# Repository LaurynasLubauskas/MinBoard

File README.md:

# MinBoard
Creator: Laurynas Lubauskas
<br>
Maintainer: Laurynas Lubauskas
<br>
MinBoard is a mini 3x3 keyboard that can *literally* fit in your pocket and is a way cheaper option than a streamdeck.
## About The Project
I made this project, because I am love fiddeling with tech and I hope it will be fun to build. This project was fun to make. It is my first "big" project. It had it's ups and downs, which I liked. In the future I might make another version of the MinBoard but that could happen in the distant future. This project has minimal codind required so if you are not familiar with coding don't worry. I think this would be a fun project for anyone who like diy or fiddeling with tech.
## Components
MinBoard contains 9 keys in total. My version of it uses the "Cherry MX Red" switches, but you can use your prefered switches. The whole keyboard is controlled by a "Seeed XIAO RP2040" microcontroller using qmk software. My version of this keyboard will use the transparent black keycaps, I think they are a great choice as they look minimalistic and have no stickers on so you have the freedom to change each button to your preference. As it is my first project I will use an easier type of diodes, the "1N4148 DO-35" because this will be my first time soldering anything.
>The PCB

---

>The Schematics

---

>3d Case

---

>3d Plate

## Contact Me
If you have any questions don't hesitate to contact me via Email
<br>
Email: laurynas.lubauskas@gmail.com

## BOM

| **Quantity** | **Item**                            | **Price**         | **Link**                                                                                                                                                                                                                                                                                                                                                                     |
| ------------ | ----------------------------------- | ----------------- | ---------------------------------------------------------------------------------------------------------------------------------------------------------------------------------------------------------------------------------------------------------------------------------------------------------------------------------------------------------------------------- |
| 9            | Cherry MX Red Switches              | 4.41€ / 5.08$     | [Link](https://fr.aliexpress.com/item/1005007891400560.htmlmp=1&pdp_npi=5@dis!EUR!EUR%204.41!EUR%204.41!!EUR%204.41!!!@211b655217621227696674886ed64a!12000042740647793!ct!LU!6001686758!!1!0&_gl=1*a0o1rq*_gcl_au*MzUxMzgzNTMyLjE3NjIwMzE5Mjc.*_ga*NjMyNjk0MjQ1LjE3NjIwMzE5Mjc.*_ga_VED1YSGNC7*czE3NjIxMjIxNTkkbzUkZzEkdDE3NjIxMjI3NjkkajI4JGwwJGgw&gatewayAdapt=glo2fra)   |
| 9            | 1N4148 DO-35 Diodes                 | 2.14€ / 2.47$     | [Link](https://fr.aliexpress.com/item/1005009623489970.html?mp=1&pdp_npi=5@dis!EUR!EUR%204.47!EUR%202.14!!EUR%202.14!!!@211b655217621227696674886ed64a!12000049679669844!ct!LU!6001686758!!1!0&_gl=1*1r24189*_gcl_au*MzUxMzgzNTMyLjE3NjIwMzE5Mjc.*_ga*NjMyNjk0MjQ1LjE3NjIwMzE5Mjc.*_ga_VED1YSGNC7*czE3NjIxMjIxNTkkbzUkZzEkdDE3NjIxMjMwMjkkajYwJGwwJGgw&gatewayAdapt=glo2fra) |
| 1            | Seeed Xiao RP2040                   | 6.99€ / 8.05$     | [Link](https://fr.aliexpress.com/item/1005003901735765.html?mp=1&pdp_npi=5@dis!EUR!EUR%2010.92!EUR%206.99!!EUR%206.99!!!@211b655217621227696674886ed64a!12000027424449312!ct!LU!6001686758!!1!0&_gl=1*o3cj8t*_gcl_au*MzUxMzgzNTMyLjE3NjIwMzE5Mjc.*_ga*NjMyNjk0MjQ1LjE3NjIwMzE5Mjc.*_ga_VED1YSGNC7*czE3NjIxMjIxNTkkbzUkZzEkdDE3NjIxMjMwNjYkajIzJGwwJGgw&gatewayAdapt=glo2fra) |
| 9            | Black-Transparent Keycaps           | 3.18€ / 3.66$     | [Link](https://fr.aliexpress.com/item/1005005514406952.html?mp=1&pdp_npi=5@dis!EUR!EUR%203.18!EUR%203.18!!EUR%203.18!!!@211b655217621227696674886ed64a!12000033372744478!ct!LU!6001686758!!1!0&_gl=1*bu5ilb*_gcl_au*MzUxMzgzNTMyLjE3NjIwMzE5Mjc.*_ga*NjMyNjk0MjQ1LjE3NjIwMzE5Mjc.*_ga_VED1YSGNC7*czE3NjIxMjIxNTkkbzUkZzEkdDE3NjIxMjMwNzIkajE3JGwwJGgw&gatewayAdapt=glo2fra)  |
| 1            | 3d Printed Case                     | N/A               | N/A                                                                                                                                                                                                                                                                                                                                                                          |
| 1            | 3d Printed Plate                    | N/A               | N/A                                                                                                                                                                                                                                                                                                                                                                          |
| 4            | M2 6mm Screws                       | 1.41€ / 1.62$     | [Link](https://fr.aliexpress.com/item/1005007264845313.html?mp=1&pdp_npi=5@dis!EUR!EUR%201.49!EUR%201.41!!EUR%201.41!!!@211b655217621227696674886ed64a!12000039998989024!ct!LU!6001686758!!1!0&_gl=1*1tnw096*_gcl_au*MzUxMzgzNTMyLjE3NjIwMzE5Mjc.*_ga*NjMyNjk0MjQ1LjE3NjIwMzE5Mjc.*_ga_VED1YSGNC7*czE3NjIxMjIxNTkkbzUkZzEkdDE3NjIxMjMxMDEkajYwJGwwJGgw&gatewayAdapt=glo2fra) |
| 4            | M2 8mm Standoffs                    | 1.87€ / 2.15$     | [Link](https://fr.aliexpress.com/item/1005007526941573.html?mp=1&pdp_npi=5@dis!EUR!EUR%202.01!EUR%201.87!!EUR%201.87!!!@211b655217621227696674886ed64a!12000041166342257!ct!LU!6001686758!!1!0&_gl=1*1ym2fc9*_gcl_au*MzUxMzgzNTMyLjE3NjIwMzE5Mjc.*_ga*NjMyNjk0MjQ1LjE3NjIwMzE5Mjc.*_ga_VED1YSGNC7*czE3NjIxMjIxNTkkbzUkZzEkdDE3NjIxMjMyNjMkajU5JGwwJGgw&gatewayAdapt=glo2fra) |
| 4            | Rubber Feet                         | 3.10€ / 3.57$     | [Link](https://fr.aliexpress.com/item/1005004068119765.html?mp=1&pdp_npi=5@dis!EUR!EUR%203.10!EUR%203.10!!EUR%203.10!!!@211b655217621227696674886ed64a!12000027931007348!ct!LU!6001686758!!1!0&_gl=1*av4qe7*_gcl_au*MzUxMzgzNTMyLjE3NjIwMzE5Mjc.*_ga*NjMyNjk0MjQ1LjE3NjIwMzE5Mjc.*_ga_VED1YSGNC7*czE3NjIxMjIxNTkkbzUkZzEkdDE3NjIxMjMyODUkajM3JGwwJGgw&gatewayAdapt=glo2fra)  |
| 1            | Pcb                                 | 6.85€ / 7.90$     | Photo in img folder                                                                                                                                                                                                                                                                                                                                                          |                                                                                                                                                                                                                                                                      |                  
| N/A          | Total Price (including shipping)    | 34.65€ / 39,95$   | N/A                                                                                                                                                                                                                                                                                                                                                                          |

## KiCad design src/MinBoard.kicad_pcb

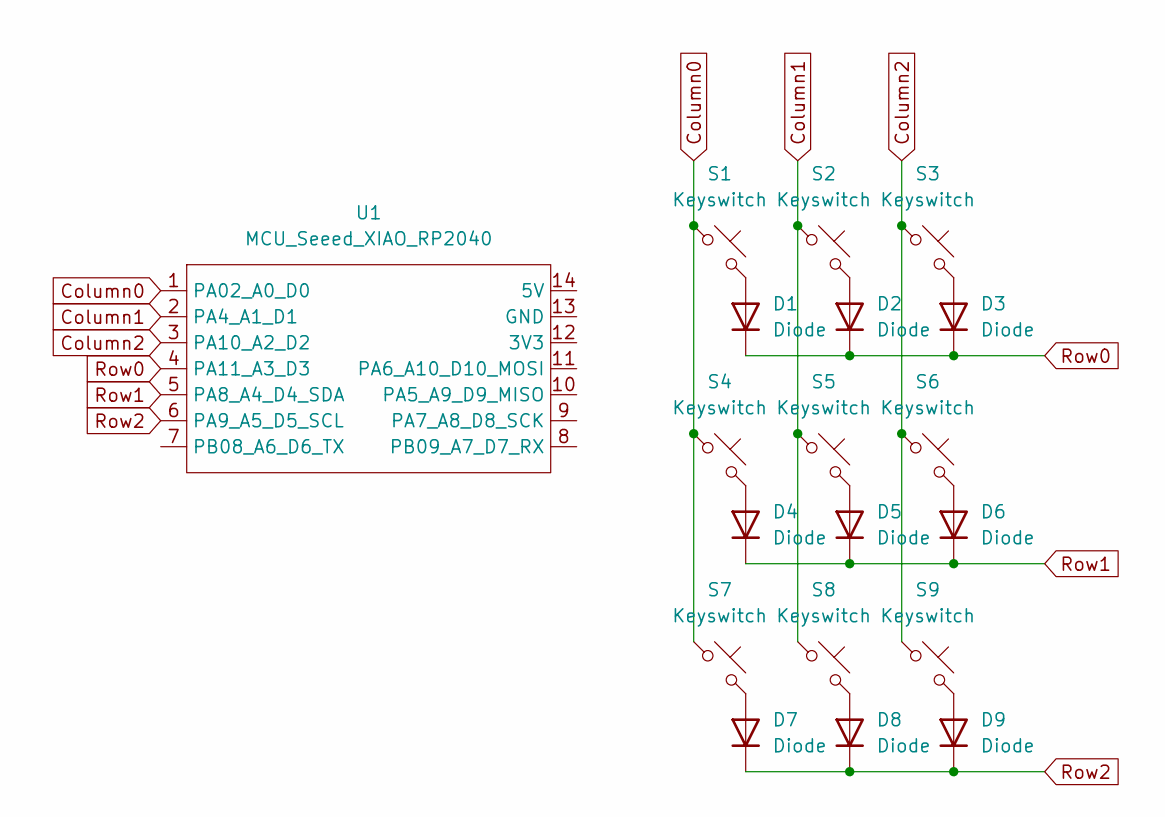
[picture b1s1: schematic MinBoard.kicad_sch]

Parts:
D1, D2, D3, D4, D5, D6, D7, D8, D9: Diode; Diode_DO-35
S1, S2, S3, S4, S5, S6, S7, S8, S9: Keyswitch; MX_PCB_1.00u
U1: MCU_Seeed_XIAO_RP2040; Seeed_XIAO_RP2040

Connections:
Column0: S1.1, S4.1, S7.1, U1.1 (PA02_A0_D0)
Column1: S2.1, S5.1, S8.1, U1.2 (PA4_A1_D1)
Column2: S3.1, S6.1, S9.1, U1.3 (PA10_A2_D2)
unnamed: D1.2 (A), S1.2
unnamed: D2.2 (A), S2.2
unnamed: D3.2 (A), S3.2
unnamed: D4.2 (A), S4.2
unnamed: D5.2 (A), S5.2
unnamed: D6.2 (A), S6.2
unnamed: D7.2 (A), S7.2
unnamed: D8.2 (A), S8.2
unnamed: D9.2 (A), S9.2
Row0: D1.1 (K), D2.1 (K), D3.1 (K), U1.4 (PA11_A3_D3)
Row1: D4.1 (K), D5.1 (K), D6.1 (K), U1.5 (PA8_A4_D4_SDA)
Row2: D7.1 (K), D8.1 (K), D9.1 (K), U1.6 (PA9_A5_D5_SCL)

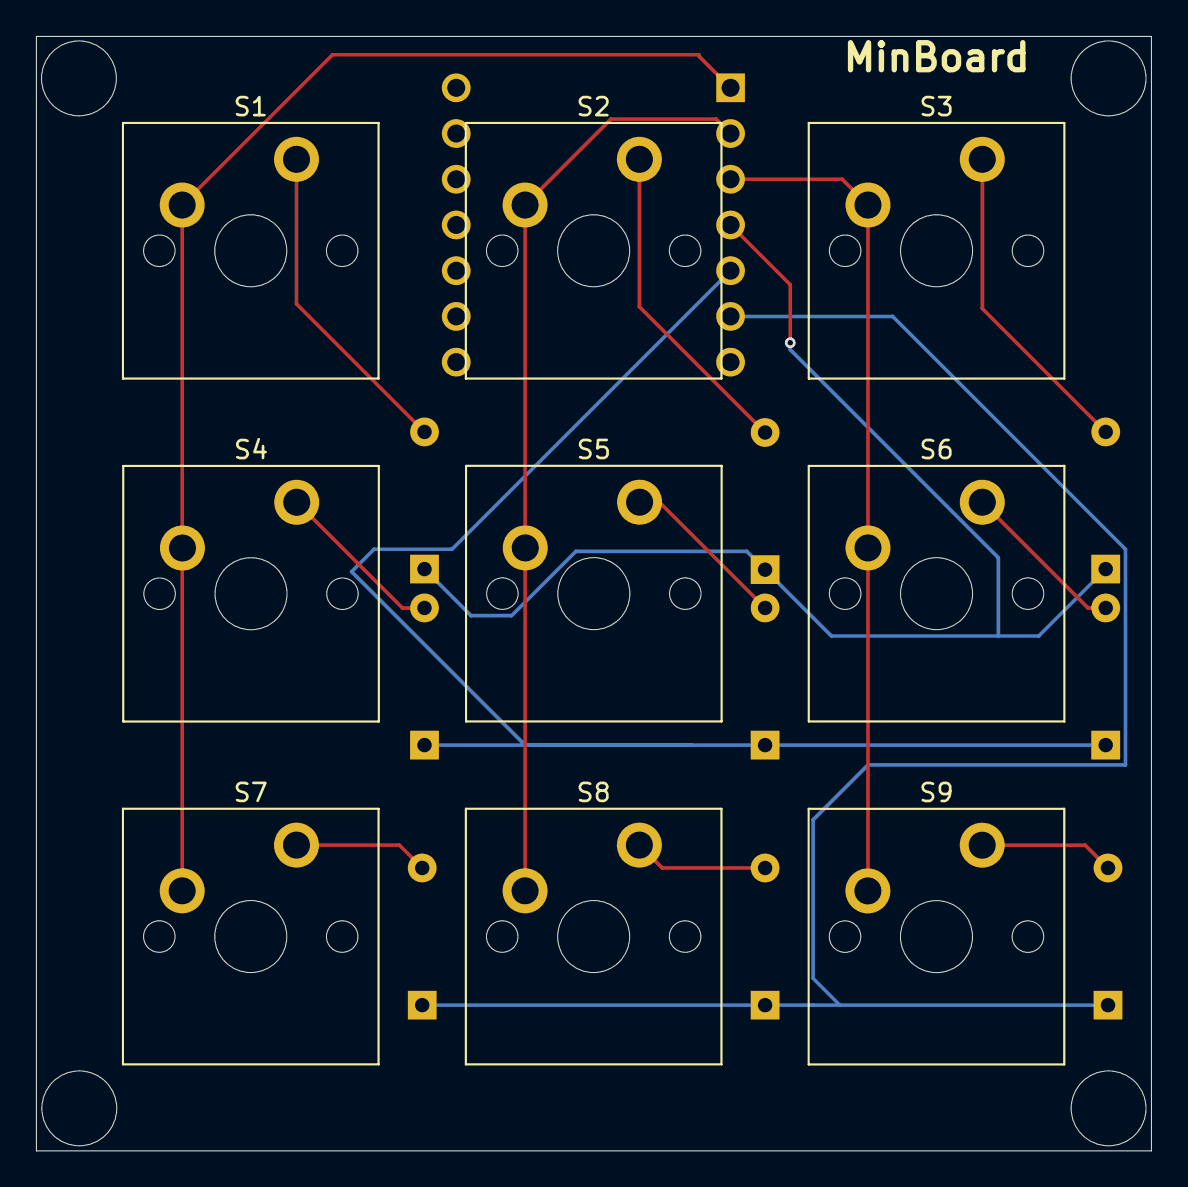
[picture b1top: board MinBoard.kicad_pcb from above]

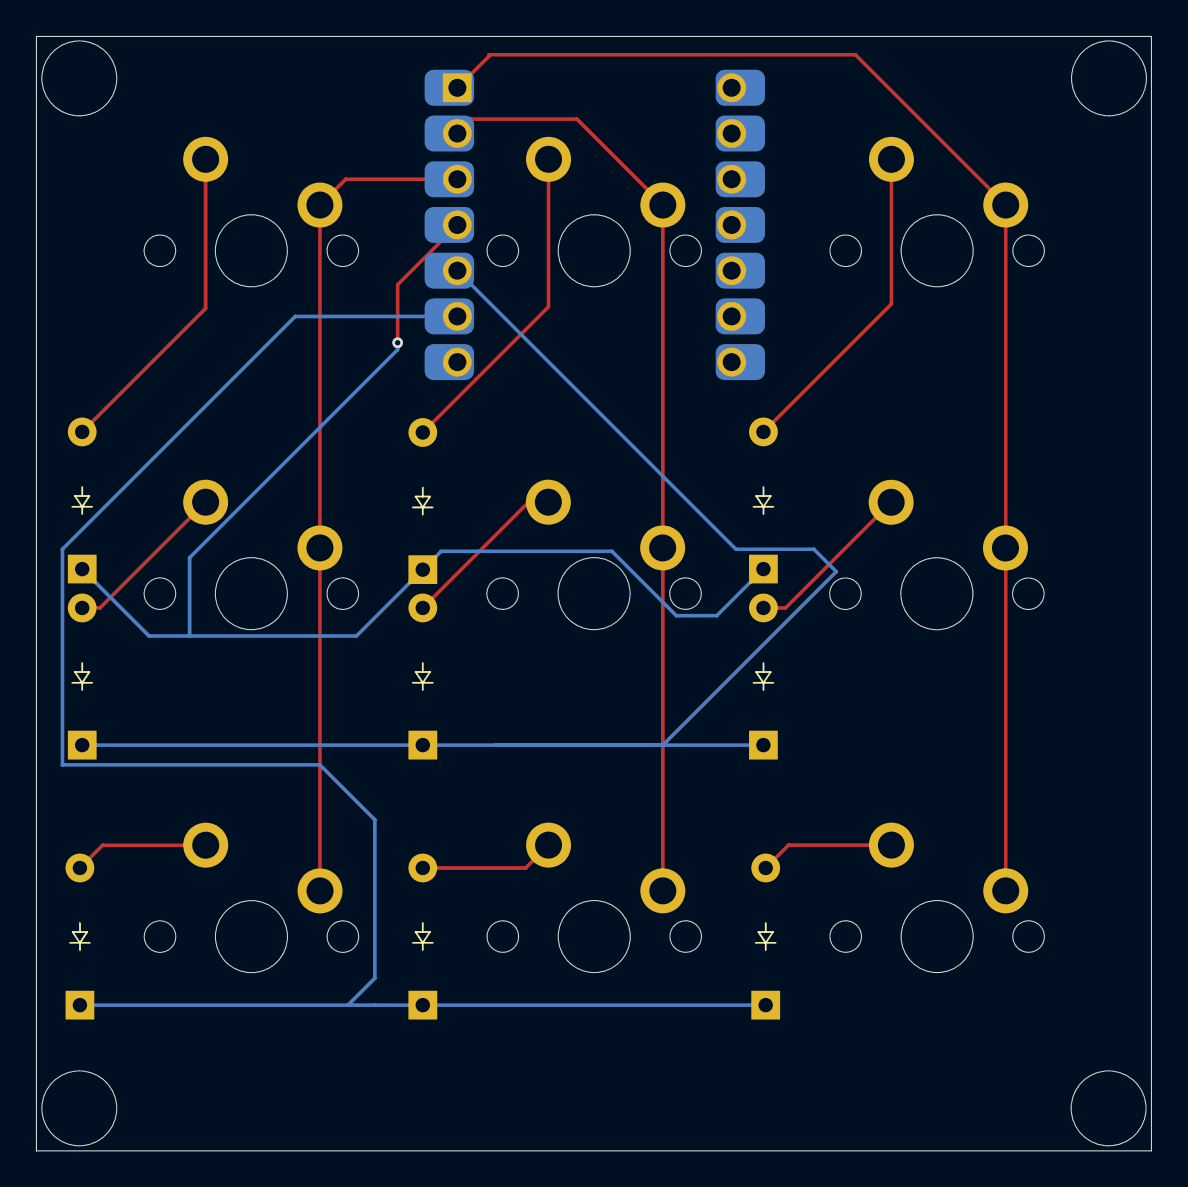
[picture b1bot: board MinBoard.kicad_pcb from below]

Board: 2 copper layers, 61.9 x 61.9 mm, 19 parts (10 on the bottom side), 15 nets.

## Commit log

2025-10-14 Create src
2025-10-14 Create del
2025-10-14 Added kicad files
2025-10-14 Right files
2025-10-14 Img uploaded
2025-10-14 More img
2025-10-14 Added holes for the screws
2025-10-14 Holes added for the pcb
2025-10-23 Add keyboard configuration for MinBoard
2025-10-23 Add initial keymap definition for 3x3 layout
2025-10-24 Add rules.mk for keyboard configuration
2025-10-24 Update readme with bootloader instructions
    Added instructions for bootloader options and troubleshooting tips.
2025-10-24 Add BOM information to keyboard readme
    Added BOM information to the readme.
2025-10-25 Add info.json for Minboard keyboard configuration
2025-10-25 Change MCU value to uppercase 'RP2040'
2025-10-25 Update readme with folder naming instructions
    Added important instructions for folder naming.
2025-11-01 Plate design created
2025-11-02 Made clearance between microcontroller and pcb
2025-11-02 JlcCart
2025-11-02 PcbDetails
2025-11-02 img change
2025-11-02 Initialize README with project overview
    Add project description and details about MinBoard.
2025-11-02 Enhance README with project details and images
    Added creator and maintainer details, project context, and updated components section with additional information and images.
2025-11-03 Update README with project details and images
    Revised project description for clarity and added sections for 3D case and plate images.
2025-11-03 Updated kicad files
2025-11-03 Update image for 3D case in README
2025-11-03 Add contact information section to README
2025-11-03 Added BOM
2025-11-03 Revise BOM with USD prices and total cost
    Updated prices to include USD equivalents and adjusted total price to reflect shipping costs.
2025-11-03 Added updated version of the BOM
2025-11-03 Modify PCB and total price in README
    Updated PCB price and total price in the table.
2025-11-10 Refine project description in README.md
    Removed repetitive phrases and fixed typos in the project description.
